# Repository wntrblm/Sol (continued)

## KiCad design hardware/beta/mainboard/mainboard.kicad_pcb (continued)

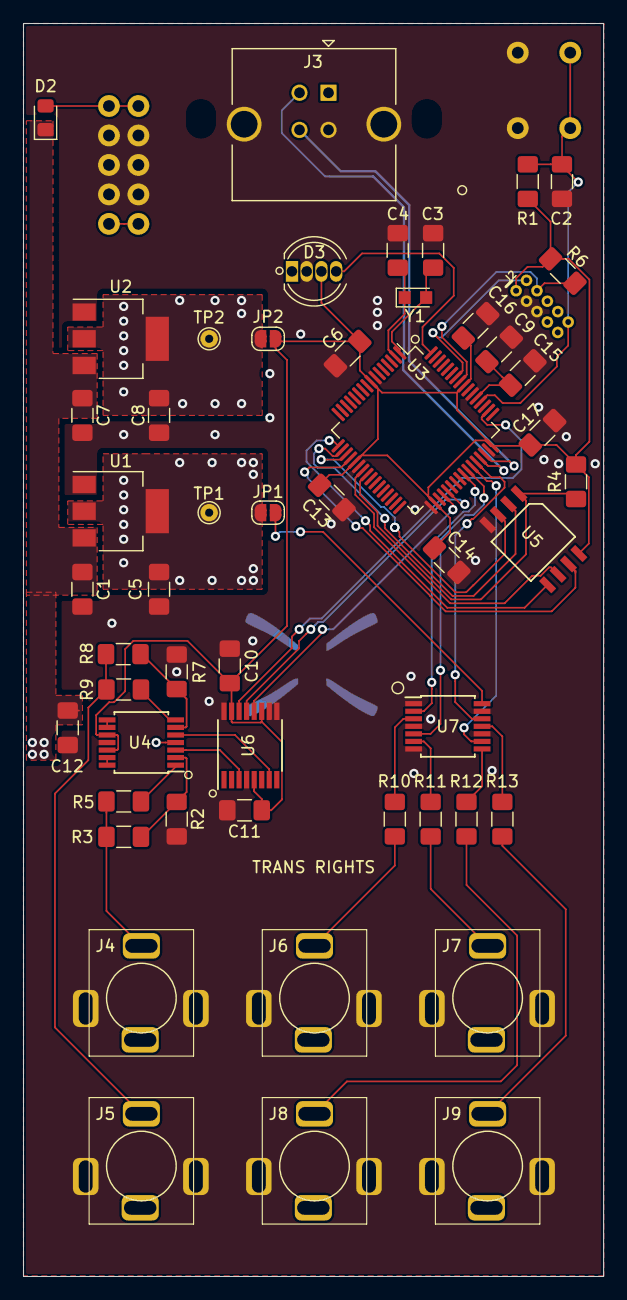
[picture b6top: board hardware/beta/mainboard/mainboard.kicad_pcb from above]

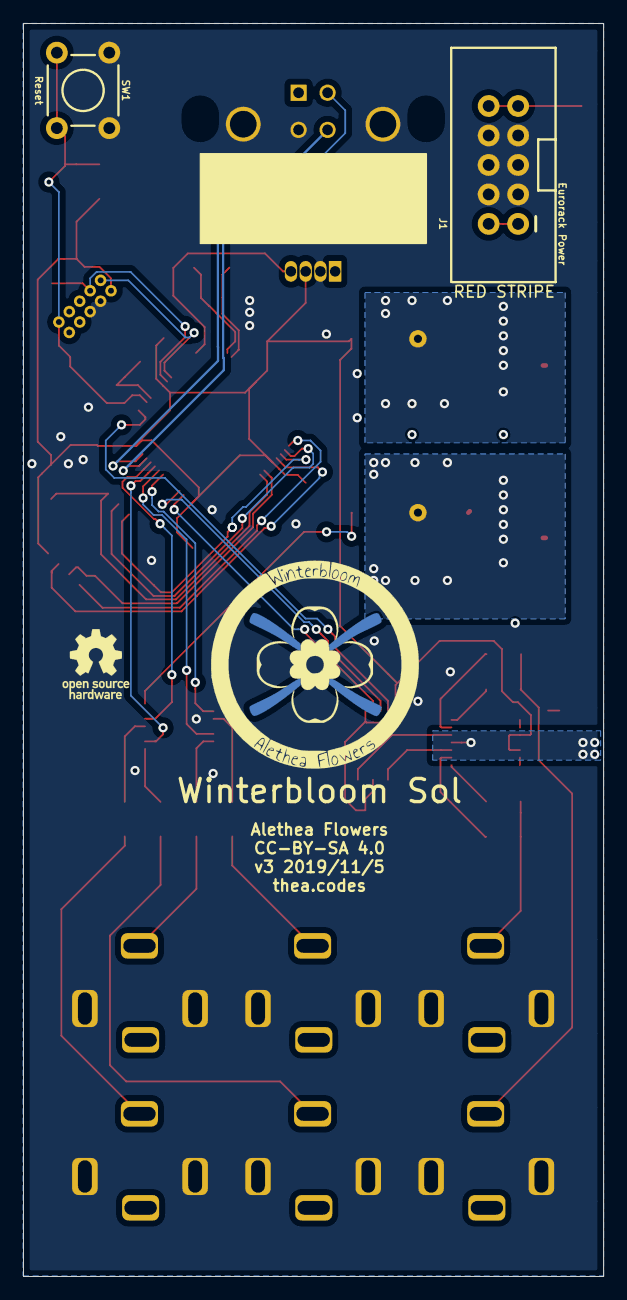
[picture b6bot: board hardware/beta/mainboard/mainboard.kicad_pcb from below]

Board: 2 copper layers, 50.0 x 108.0 mm, 55 parts (3 on the bottom side), 48 nets.

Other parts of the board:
Ref**: Val**; winterbloom-pcb-logo

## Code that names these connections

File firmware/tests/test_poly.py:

# Copyright (c) 2019 Alethea Flowers for Winterbloom
# Licensed under the MIT License

from unittest import mock

import winterbloom_smolmidi as smolmidi
from winterbloom_sol import helpers, poly, sol

_NS_TO_S = 1000000000


def make_message(type, *data):
    msg = smolmidi.Message()
    msg.type = type
    msg.data = data
    return msg


@mock.patch("time.monotonic_ns", autospec=True)
def test_poly_note_stealing(monotonic_ns):
    state = sol.State()
    outputs = sol.Outputs()

    p = poly.Poly()

    # No notes, all outputs should be default states.
    monotonic_ns.return_value = 0
    p.update(state, outputs)

    assert outputs.cv_a == 0
    assert outputs.cv_b == 0
    assert outputs.cv_c == 0
    assert outputs.cv_d == 0
    assert outputs.gate_1 is False
    assert outputs.gate_2 is False
    assert outputs.gate_3 is False
    assert outputs.gate_4 is False

    # Play one note, assert that it gets assigned.
    state.message = make_message(smolmidi.NOTE_ON, 40, 127)
    p.update(state, outputs)

    assert outputs.cv_a == helpers.note_to_volts_per_octave(40)
    assert outputs.cv_b == 0
    assert outputs.cv_c == 0
    assert outputs.cv_d == 0
    assert outputs.gate_1 is True
    assert outputs.gate_2 is False
    assert outputs.gate_3 is False
    assert outputs.gate_4 is False

    # Release the note, assert that it's gate gets released.
    monotonic_ns.return_value = 1 * _NS_TO_S
    state.message = make_message(smolmidi.NOTE_OFF, 40)
    p.update(state, outputs)

    assert outputs.gate_1 is False

    # Play four notes, assert that they all get assigned.
    monotonic_ns.return_value = 1 * _NS_TO_S
    state.message = make_message(smolmidi.NOTE_ON, 40, 127)
    p.update(state, outputs)
    monotonic_ns.return_value = 2 * _NS_TO_S
    state.message = make_message(smolmidi.NOTE_ON, 41, 127)
    p.update(state, outputs)
    monotonic_ns.return_value = 3 * _NS_TO_S
    state.message = make_message(smolmidi.NOTE_ON, 42, 127)
    p.update(state, outputs)
    monotonic_ns.return_value = 4 * _NS_TO_S
    state.message = make_message(smolmidi.NOTE_ON, 43, 127)
    p.update(state, outputs)

    assert outputs.cv_a == helpers.note_to_volts_per_octave(40)
    assert outputs.cv_b == helpers.note_to_volts_per_octave(41)
    assert outputs.cv_c == helpers.note_to_volts_per_octave(42)
    assert outputs.cv_d == helpers.note_to_volts_per_octave(43)
    assert outputs.gate_1 is True
    assert outputs.gate_2 is True
    assert outputs.gate_3 is True
    assert outputs.gate_4 is True

    # Play one more note, it should replace the oldest (first)
    # note.
    state.message = make_message(smolmidi.NOTE_ON, 44, 127)
    p.update(state, outputs)

    assert outputs.cv_a == helpers.note_to_volts_per_octave(44)

    # This should cause retrigger, so it should go False briefly
    # then go to True. step() must be called to update the gate
    # retrigger logic.
    assert outputs.gate_1 is False
    monotonic_ns.return_value = 5 * _NS_TO_S
    outputs.step()
    assert outputs.gate_1 is True

    # Release one of the notes in the middle. It should create
    # a "hole".
    state.message = make_message(smolmidi.NOTE_OFF, 42)
    p.update(state, outputs)

    assert outputs.gate_3 is False

    # Now, play another note. It should get assigned to the
    # "hole".
    state.message = make_message(smolmidi.NOTE_ON, 45, 127)
    p.update(state, outputs)

    assert outputs.cv_c == helpers.note_to_volts_per_octave(45)
    assert outputs.gate_3 is True

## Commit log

2019-10-28 Add _midi_ext and trigger
2019-10-28 Add _utils.py
2019-10-28 Add sol.py, get it importable in tests
2019-10-28 Add tests for State
2019-10-28 Add tests for Output
2019-10-29 Update voltageio
2019-10-31 Uncomment msg
2019-10-31 Add support for Note On with 0 velocity
2019-10-31 Remove unused test file
2019-10-31 Implement enough stubs to get Sol to construct
2019-10-31 Add basic test for run
2019-10-31 Re-blacken
2019-10-31 Test different message types
2019-11-01 Add retrigger
2019-11-01 Add basic helpers
2019-11-01 Add example, add MIDI transport, make ccs 0-1
2019-11-01 Add MIDI clock
2019-11-01 Update sample
2019-11-01 Fix typo
2019-11-02 Add __init__.py
2019-11-02 Small fixes from testing MIDI clock
2019-11-04 Re-blacken, fix isort
2019-11-09 Move note strategies into properties
2019-11-09 Update ad5689
2019-11-10 Add ADSR
2019-11-11 Stop calling gc.collect every loop
2019-11-25 Switch ADSR to monotonic_ns
2019-11-25 Add slew limiter
2019-11-25 Add SlewLimiter to winterbloom_sol/__init__.py
2019-11-25 Add missing files..
2019-11-26 Use isclose to compare floats
2019-12-03 Add assembly test program
2019-12-03 Fix bug in example program (was using old API)
2019-12-03 Add slew limiter example
2019-12-03 Add ADSR example
2019-12-05 Decorate some stuff with @micropython.native
2019-12-05 Add clocks example
2019-12-05 Add colorwheel function
2019-12-05 Move status LED to the Outputs class
2019-12-20 Move software into the firmware directory to prepare for hardware files
2019-12-20 Add hardware license
2019-12-20 Add beta mainboard hardware design files
2019-12-20 Add beta panel hardware design files
2019-12-20 Add breakouts
2019-12-20 Add experimental deployment script
2019-12-21 Update the deploy script to prepare a bundle instead of uploading directly to the device
2020-01-11 Add first run at mainboard for rev1
2020-01-11 Remove old revision of mainboard
2020-01-12 Switch 3v3 regulator to TPS796
2020-01-13 Replace voltage reference buffer with OPA388
2020-01-13 Re-route the +12v trace and do a bunch of ground stitching
2020-01-14 Finish up mainboard - place silkscreen, add branding, etc.
2020-01-15 Fix some component sizes
2020-01-15 Move to the AD5686R, drop the TMUX
2020-01-15 Update some cap sizes
2020-01-15 Assign MPNs to all symbols
2020-01-15 Assigning more MPNs
2020-01-15 Add PDF of schematic
2020-01-19 Add basic, unfinished jackboard
2020-01-19 Add basic, unfinished panel
2020-01-20 Add programming board
2020-01-20 Add LFO classes and an LFO example
2020-02-16 Update voltagio
2020-02-29 Add calibration script, make Sol read from calibration
2020-02-29 remove duplicated text
2020-02-29 remove duplicated text (#1)
2020-03-02 Add missing outputs to Sol
2020-03-02 Fix cv c and d outputs
2020-03-02 Fixup examples
2020-03-02 Blacken
2020-03-03 Wrap up prototype jackboard
2020-03-04 Add blank panel
2020-03-05 Make state.notes a public property
2020-03-05 Move trigger to time.monotonic_ns
2020-03-05 Add polyphonic helper and example
2020-03-05 Add reset to LFOs
2020-03-05 Add BPM/clock frequency to state
2020-03-06 Add some missing 3d moels
2020-03-06 Save and load calibration from NVM, restore beta board support
2020-03-07 Add map helper
2020-03-07 Add random sample
2020-03-12 Add experimental calibration restorer
2020-03-12 Add calibration rescure procedure to firmware
2020-04-03 Update panel and gerbers
2020-04-07 Add user guide
2020-04-07 Deployed e7882b7 with MkDocs version: 1.1
2020-04-10 Update panel with new logo
2020-04-14 Update panel
2020-04-14 Update images for user guide
2020-04-14 Deployed 686575f with MkDocs version: 1.1
2020-04-24 Ignore built user guide
2020-04-24 Update all gerbes for latest PCB revisions
2020-05-22 Add cv c and d to the default program
2020-05-22 Add firmware readme
2020-05-22 Finish factory setup script
2020-05-31 Alias aftertouch to state.pressure
2020-06-19 Add factory setup script
2020-06-19 Fixup tests
2020-06-19 Add new ADSR class
2020-06-19 Fix decay phase for re-started envelopes
2020-07-10 index: describe MIDI message object in more depth
2020-07-10 sol: add `Outputs.set_cv` to parametrically set CV
2020-07-10 index: describe MIDI message object in more depth (#3)
2020-07-11 guide: mention Outputs.set_cv
2020-07-11 outputs: set_cv uses getattr instead of a big if statement
2020-07-11 sol: add `set_gate` for parametric gate states
2020-07-11 sol: add parametric gate trigger and retrigger functions
2020-07-11 user guide: add docs for parametric gate methods
2020-07-11 sol: add parametric CV and gate value setters (#4)
    * sol: add `Outputs.set_cv` to parametrically set CV
    * guide: mention Outputs.set_cv
    * outputs: set_cv uses getattr instead of a big if statement
    * sol: add `set_gate` for parametric gate states
    * sol: add parametric gate trigger and retrigger functions
    * user guide: add docs for parametric gate methods
2020-07-12 Reduce loop overhead by changing the CC array copy strategy
2020-09-28 Modify factory setup script so that it can just deploy the code files to a local folder to make releases easier
2020-09-28 Rename experimental directory to factory
2020-09-28 Deployed e1ef903 with MkDocs version: 1.1.2
2020-10-03 Remove micropython.native in helpers, as it seems to be buggy
2020-10-10 Use custom theme for user guide
2020-10-10 Deployed 9a73ba7 with MkDocs version: 1.1.2
2020-10-10 user guide: mention JACK MIDI and `a2jmidid`
2020-10-10 user guide: mention JACK MIDI and `a2jmidid` (#6)
2020-10-10 Deployed ef39ab7 with MkDocs version: 1.1.2
2020-10-20 Fixup user guide theme
2020-10-27 Refine the factory setup script a little more: automatically detect when drvives are available and detect when the correct DAC channel is connected to the multimeter.
2020-10-28 Refactor a lot of the factory setup code for easier re-use
2020-10-28 Remove some debug prints, make deploy_files output nicer
2020-11-10 Make sure firmware gets placed in the right spot in flash
2020-12-12 Move docs to shared theme
2020-12-12 Update PDF of schematic and add git pre-commit hook to make sure it stays up-to-date
2020-12-12 Add open source information and links to the hardware and firmware sources
2020-12-12 Deployed f990cae with MkDocs version: 1.1.2
2020-12-13 Add link to documentation in the readme
2021-01-09 Create CNAME
2021-01-21 Add option to recalibrate during factory setup
2021-01-21 Add OSHW certification info
2021-01-21 Deployed c38bb8d with MkDocs version: 1.1.2
2021-01-22 Add CNAME
2021-01-29 docs: Add link to Liz Clark's video on Raspberry Pi MIDI host.
2021-01-29 Deployed e114968 with MkDocs version: 1.1.2
2021-01-30 Use wintertools
2021-02-13 user_guide: increase contrast, mark external links
2021-02-13 Deployed c5eaea9 with MkDocs version: 1.1.2
2021-04-04 Fixup factory setup script to work with latest wintertools
2021-04-30 factory: fix publish command
2021-04-30 firmware: fix should_trigger_clock() to only trigger when a clock message is received, fixing #7
2021-05-08 Deployed 5509873 with MkDocs version: 1.1.2
2022-10-17 Fix SPIDevice error in new versions of CircuitPython and Adafruit_Bus_Device
